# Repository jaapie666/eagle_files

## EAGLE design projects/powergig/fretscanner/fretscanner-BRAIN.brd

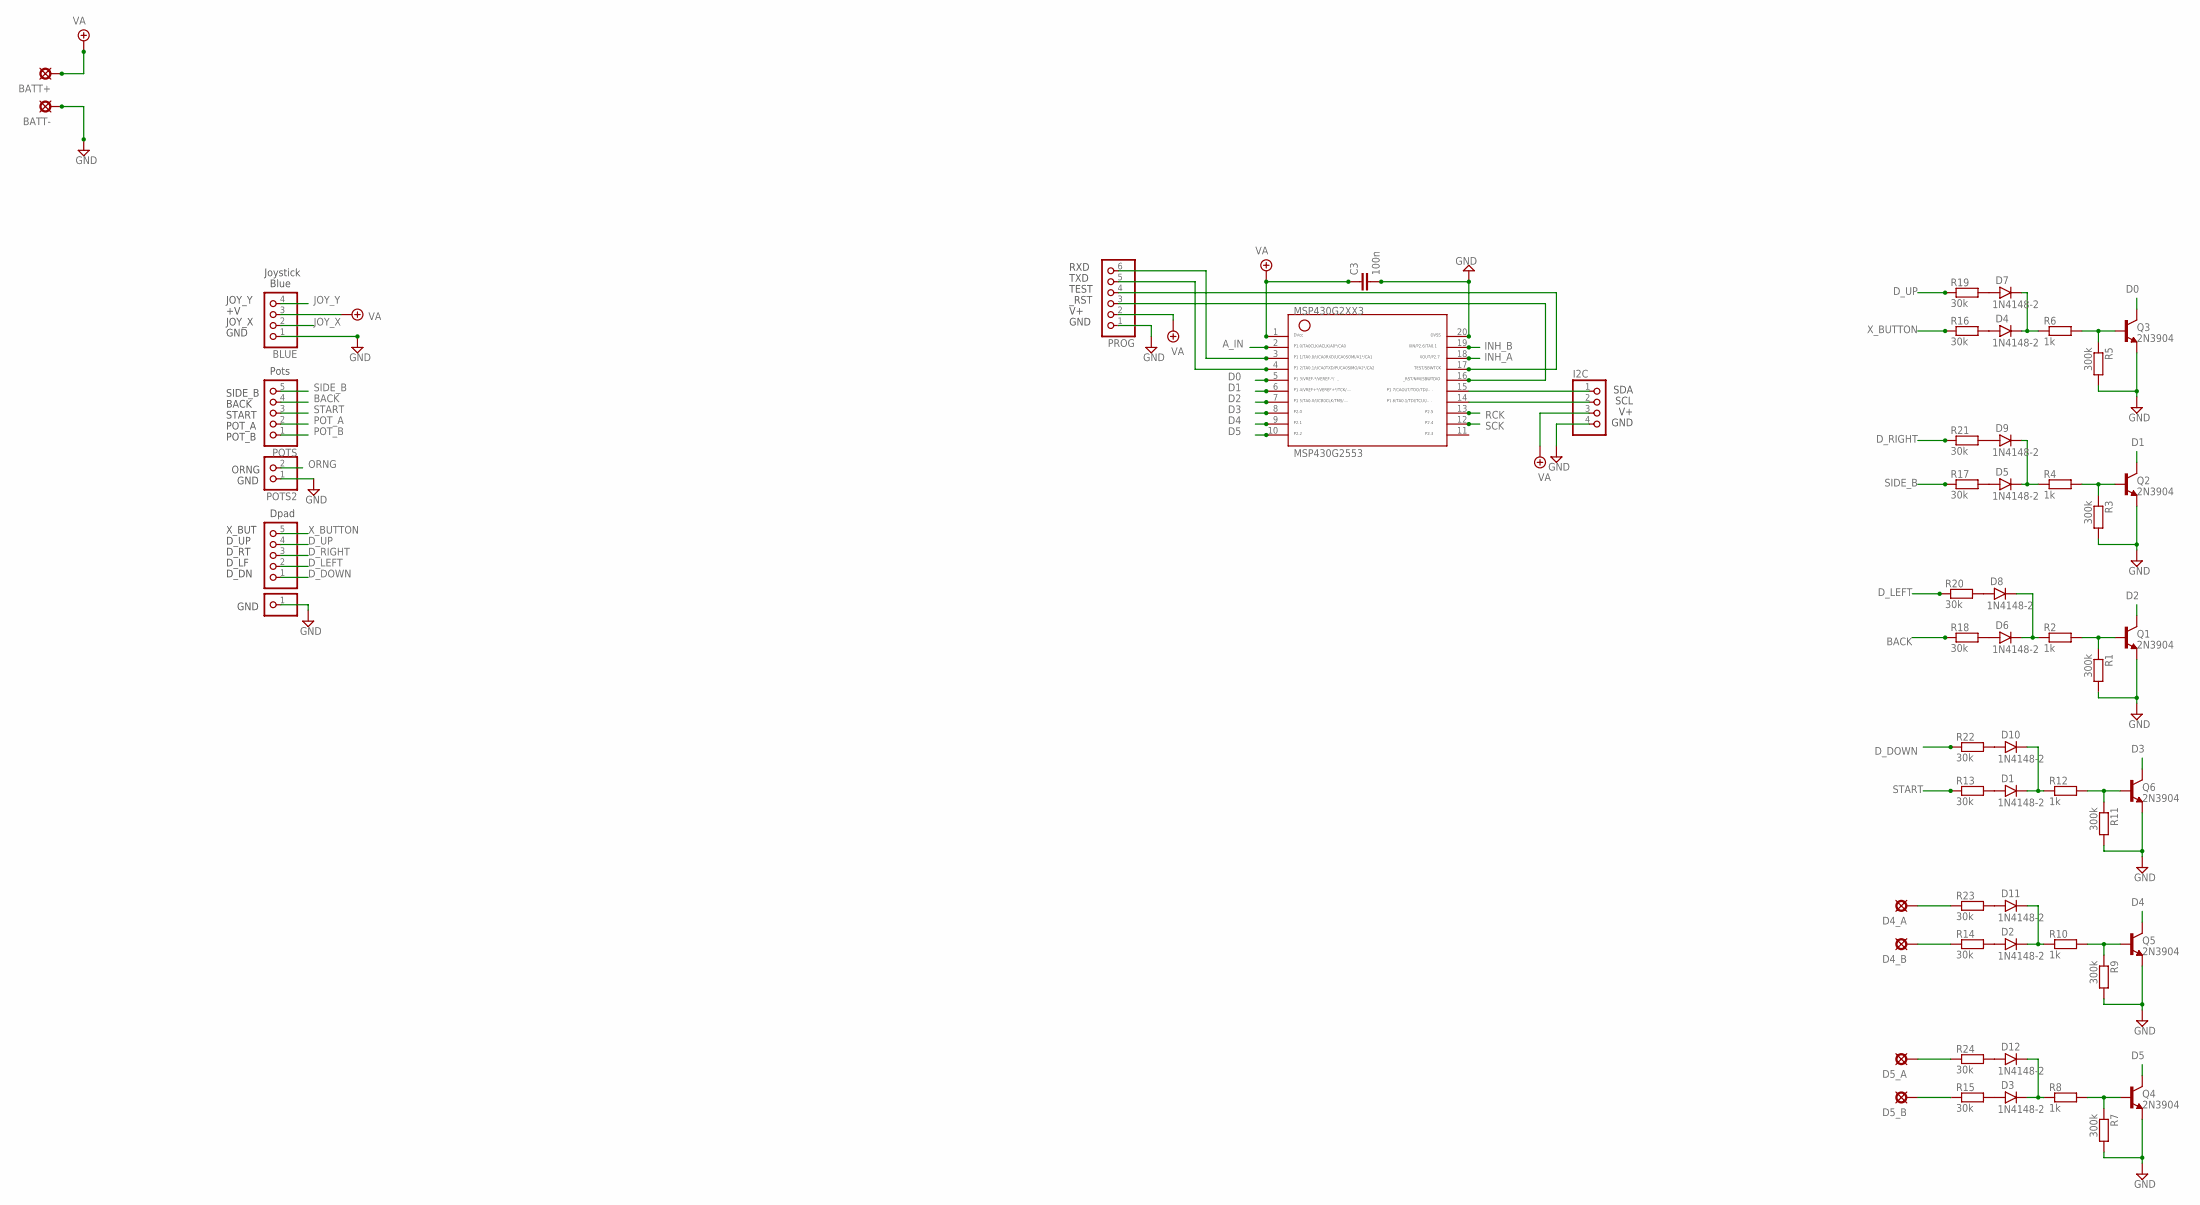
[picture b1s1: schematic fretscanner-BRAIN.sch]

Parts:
BATT+: PADL; LONG
BATT-: PADL; LONG
BLUE: PINHD-1X4; 1X04
C3: 100n; 050X030_050_3
D1, D2, D3, D4, D5, D6, D7, D8, D9, D10, D11, D12: 1N4148-2; DO35-2
D4_A, D4_B, D5_A, D5_B: PAD; SQUARE
DPAD: PINHD-1X5; 1X05
DPAD2: PINHD-1X1; 1X01
I2C: PINHD-1X4; 1X04
MSP430G2553: G2XX3---N20; N20
POTS: PINHD-1X5; 1X05
POTS2: PINHD-1X2; 1X02
PROG: PINHD-1X6; 1X06
Q1, Q2, Q3, Q4, Q5, Q6: 2N3904; TO92-
R1, R3, R5, R7, R9, R11: 300k; R0207/1V
R2, R4, R6, R8, R10, R12: 1k; R0207/3
R13, R14, R15, R16, R17, R18, R19, R20, R21, R22, R23, R24: 30k; R0207/3

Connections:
A_IN: MSP430G2553.2
BACK: POTS.4, R18.1
D0: MSP430G2553.5, Q3.1 (C)
D1: MSP430G2553.6, Q2.1 (C)
D2: MSP430G2553.7, Q1.1 (C)
D3: MSP430G2553.8, Q6.1 (C)
D4: MSP430G2553.9, Q5.1 (C)
D5: MSP430G2553.10, Q4.1 (C)
D_DOWN: DPAD.1, R22.1
D_LEFT: DPAD.2, R20.1
D_RIGHT: DPAD.3, R21.1
D_UP: DPAD.4, R19.1
GND: BATT-.1, BLUE.1, C3.2, DPAD2.1, I2C.4, MSP430G2553.20, POTS2.1, PROG.1, Q1.3 (E), Q2.3 (E), Q3.3 (E), Q4.3 (E), Q5.3 (E), Q6.3 (E), R1.2, R3.2, R5.2, R7.2, R9.2, R11.2
INH_A: MSP430G2553.18
INH_B: MSP430G2553.19
JOY_X: BLUE.2
JOY_Y: BLUE.4
unnamed: I2C.1, MSP430G2553.15
unnamed: Q2.2 (B), R3.1, R4.2
unnamed: D3.A, R15.2
unnamed: D5.C, D9.C, R4.1
unnamed: Q3.2 (B), R5.1, R6.2
unnamed: Q1.2 (B), R1.1, R2.2
unnamed: D6.C, D8.C, R2.1
unnamed: D4.A, R16.2
unnamed: D5.A, R17.2
unnamed: D4.C, D7.C, R6.1
unnamed: Q4.2 (B), R7.1, R8.2
unnamed: D6.A, R18.2
unnamed: D3.C, D12.C, R8.1
unnamed: Q5.2 (B), R9.1, R10.2
unnamed: D1.A, R13.2
unnamed: I2C.2, MSP430G2553.14
unnamed: D2.C, D11.C, R10.1
unnamed: Q6.2 (B), R11.1, R12.2
unnamed: D2.A, R14.2
unnamed: D1.C, D10.C, R12.1
unnamed: D7.A, R19.2
unnamed: D8.A, R20.2
unnamed: D9.A, R21.2
unnamed: D10.A, R22.2
unnamed: D4_B.1, R14.1
unnamed: D5_B.1, R15.1
unnamed: D11.A, R23.2
unnamed: D12.A, R24.2
unnamed: D4_A.1, R23.1
unnamed: D5_A.1, R24.1
ORNG: POTS2.2
POT_A: POTS.2
POT_B: POTS.1
RCK: MSP430G2553.13
RXD: MSP430G2553.3, PROG.6
SCK: MSP430G2553.12
SIDE_B: POTS.5, R17.1
START: POTS.3, R13.1
TEST: MSP430G2553.17, PROG.4
TXD: MSP430G2553.4, PROG.5
VA: BATT+.1, BLUE.3, C3.1, I2C.3, MSP430G2553.1, PROG.2
X_BUTTON: DPAD.5, R16.1
_RST: MSP430G2553.16, PROG.3

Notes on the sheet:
Joystick
Pots
Dpad
Blue
X_BUT
D_UP
D_RT
D_LF
D_DN
GND
SIDE_B
BACK
START
POT_A
POT_B
ORNG
JOY_X
JOY_Y
RXD
TXD
TEST
_RST
SDA
SCL

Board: 2 copper layers, 57 parts (0 on the bottom side), 50 nets, no tracks yet.

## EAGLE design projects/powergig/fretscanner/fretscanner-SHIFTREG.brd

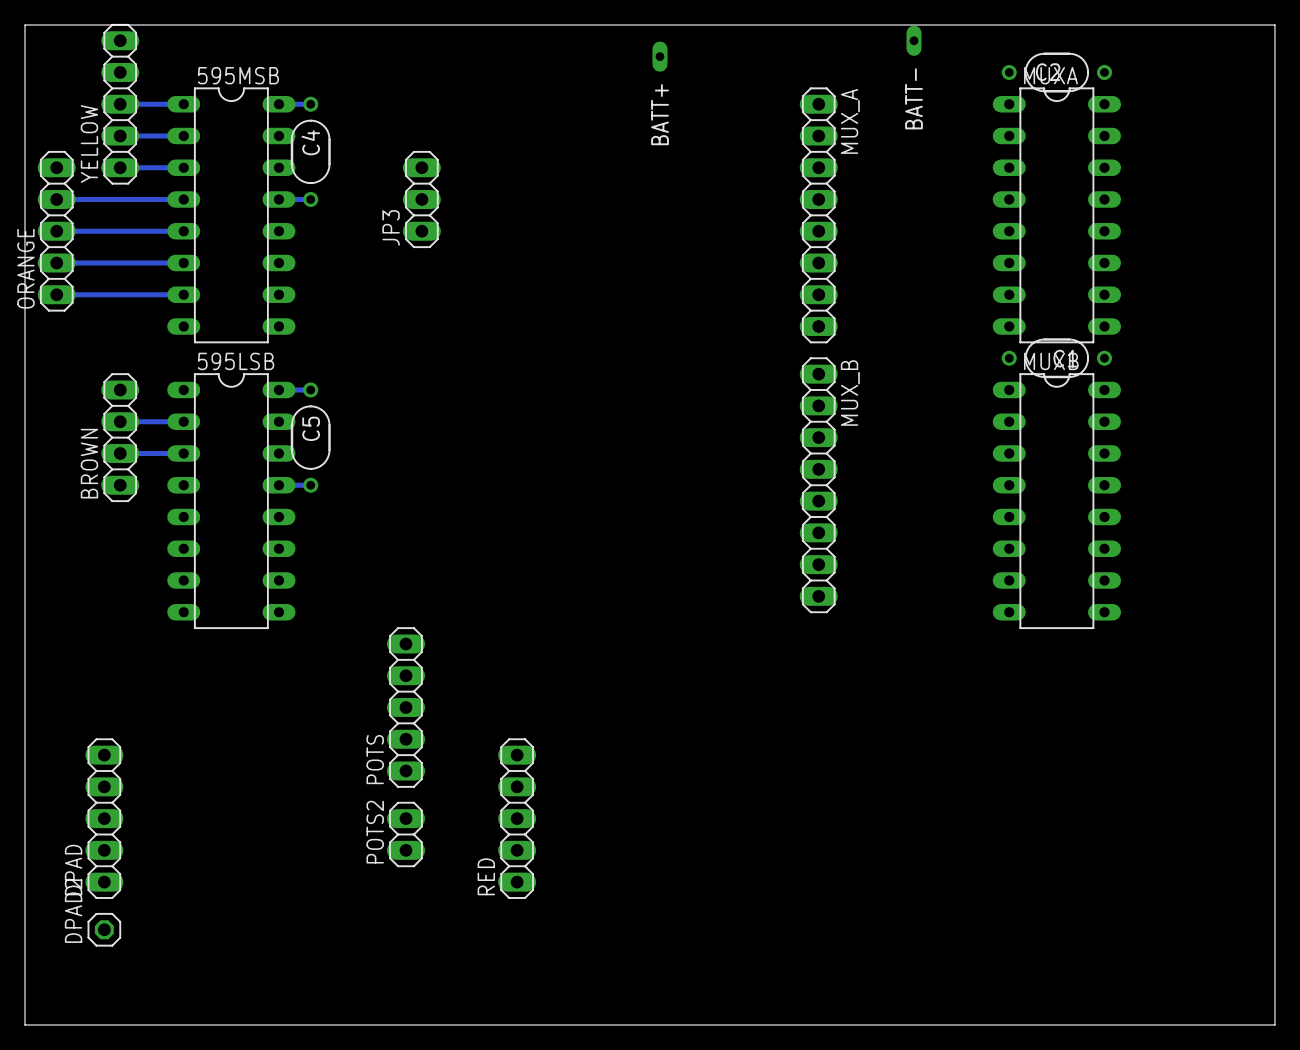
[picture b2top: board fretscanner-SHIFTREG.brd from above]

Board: 2 copper layers, 100.0 x 80.0 mm, 21 parts (0 on the bottom side), 38 nets.

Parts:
595LSB, 595MSB: 74LS595N; DIL16
BATT+: LONG
BATT-: LONG
BROWN: 1X04
C1, C2, C4, C5: 100n; 050X030_050_3
DPAD: 1X05
DPAD2: 1X01
JP3: 1X03
MUXA: 4051N; DIL16
MUXB: 4051N; DIL16
MUX_A: 1X08
MUX_B: 1X08
ORANGE: 1X05
POTS: 1X05
POTS2: 1X02
RED: 1X05
YELLOW: 1X05

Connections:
A_IN: MUXA.3, MUXB.3
GND: 595LSB.8, 595LSB.13, 595MSB.8, 595MSB.13, BATT-.1, BROWN.1, C1.2, C2.2, C4.2, C5.2, DPAD2.1, MUXA.7, MUXA.8, MUXB.7, MUXB.8, POTS2.1
JOY_X: MUXA.4, MUX_A.1
JOY_Y: MUXA.2, MUX_A.2
MUX09: MUXA.13, MUX_A.8
unnamed: 595LSB.14, 595MSB.9
unnamed: MUXA.12, MUX_A.5
unnamed: MUXA.15, MUX_A.6
unnamed: MUXA.14, MUX_A.7
unnamed: MUXB.4, MUX_B.1
unnamed: MUXB.2, MUX_B.2
unnamed: MUXB.5, MUX_B.3
unnamed: MUXB.1, MUX_B.4
unnamed: MUXB.12, MUX_B.5
unnamed: MUXB.15, MUX_B.6
unnamed: MUXB.14, MUX_B.7
unnamed: MUXB.13, MUX_B.8
POT_A: MUXA.5, MUX_A.3, POTS.2
POT_B: MUXA.1, MUX_A.4, POTS.1
RCK: 595LSB.12, 595MSB.12, JP3.2
SCK: 595LSB.11, 595MSB.11, JP3.1
SER: 595MSB.14, JP3.3
SR0: 595LSB.7, MUXA.11, MUXB.11
SR1: 595LSB.6, MUXA.10, MUXB.10
SR2: 595LSB.5, MUXA.9, MUXB.9
SR4: 595LSB.3, BROWN.2
SR5: 595LSB.2, BROWN.3
SR6: 595LSB.1, YELLOW.5
SR7: 595LSB.15, BROWN.4
SR8: 595MSB.7, ORANGE.1
SR9: 595MSB.6, ORANGE.2
SR10: 595MSB.5, ORANGE.3
SR11: 595MSB.4, ORANGE.4
SR12: 595MSB.3, YELLOW.1
SR13: 595MSB.2, YELLOW.2
SR14: 595MSB.1, YELLOW.3
SR15: 595MSB.15, YELLOW.4
VA: 595LSB.10, 595LSB.16, 595MSB.10, 595MSB.16, BATT+.1, C1.1, C2.1, C4.1, C5.1, MUXA.16, MUXB.16

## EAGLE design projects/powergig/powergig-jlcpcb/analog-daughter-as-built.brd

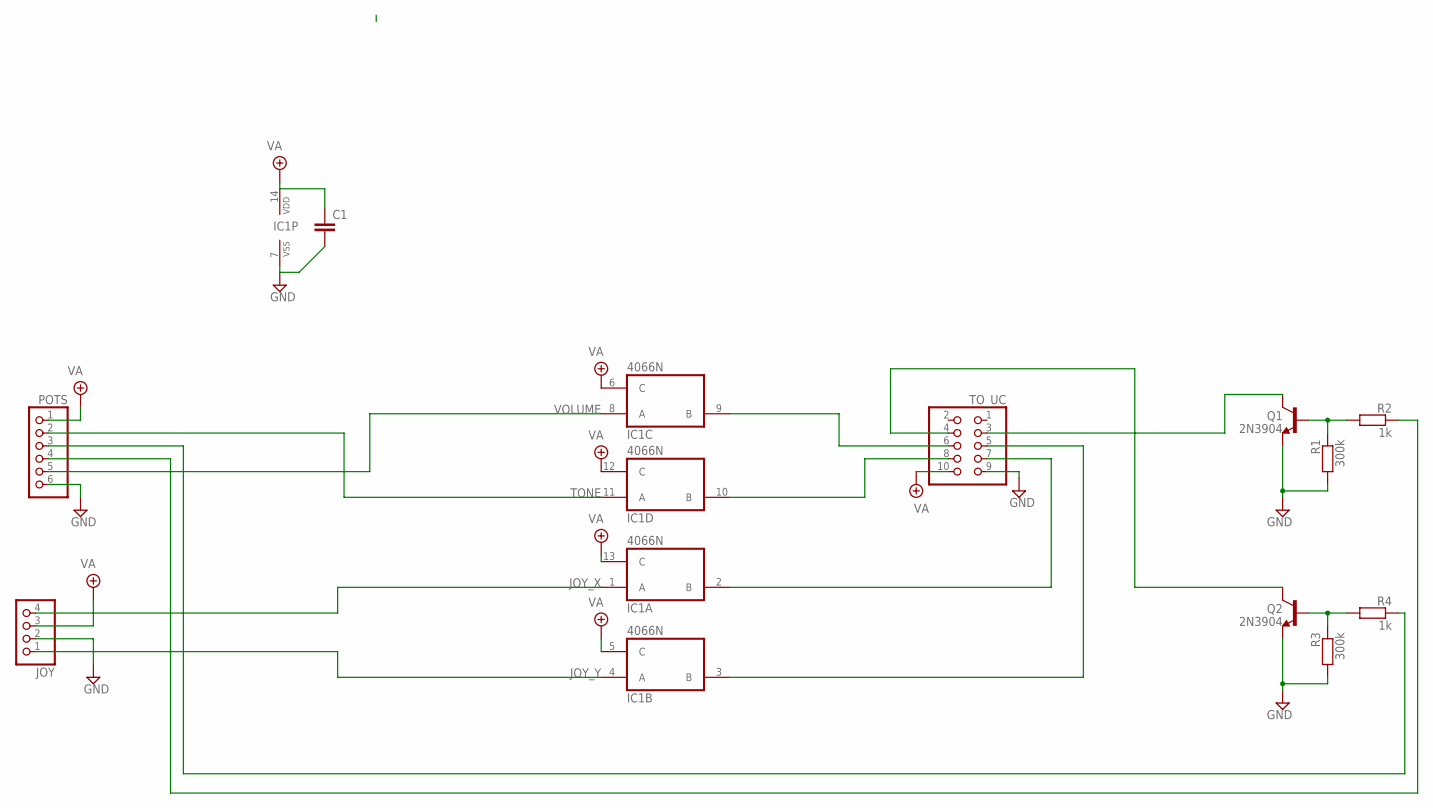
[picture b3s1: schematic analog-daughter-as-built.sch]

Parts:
C1: 050X030_0251; 050X030_025
IC1: 4066N; DIL14
JOY: PINHD-1X4; 1X04
POTS: PINHD-1X6; 1X06
Q1, Q2: 2N3904; TO92-
R1, R3: 300k; R0207/3
R2, R4: 1k; R0207/3
TO_UC: PINHD-2X5IDC; 10PIN_IDC

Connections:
GND: C1.2, IC1.7 (VSS), JOY.2, POTS.6, Q1.3 (E), Q2.3 (E), R1.2, R3.2, TO_UC.9
JOY_X: IC1.1 (A), JOY.4
JOY_Y: IC1.4 (A), JOY.1
unnamed: Q1.1 (C), TO_UC.3
unnamed: IC1.9 (B), TO_UC.6
unnamed: IC1.10 (B), TO_UC.8
unnamed: IC1.2 (B), TO_UC.7
unnamed: IC1.3 (B), TO_UC.5
unnamed: Q2.1 (C), TO_UC.4
unnamed: Q1.2 (B), R1.1, R2.2
unnamed: Q2.2 (B), R3.1, R4.2
TONE: IC1.11 (A), POTS.2
TONE_BUTTON: POTS.3, R4.1
VA: C1.1, IC1.5 (C), IC1.6 (C), IC1.12 (C), IC1.13 (C), IC1.14 (VDD), JOY.3, POTS.1, TO_UC.10
VOLUME: IC1.8 (A), POTS.5
VOL_BUTTON: POTS.4, R2.1

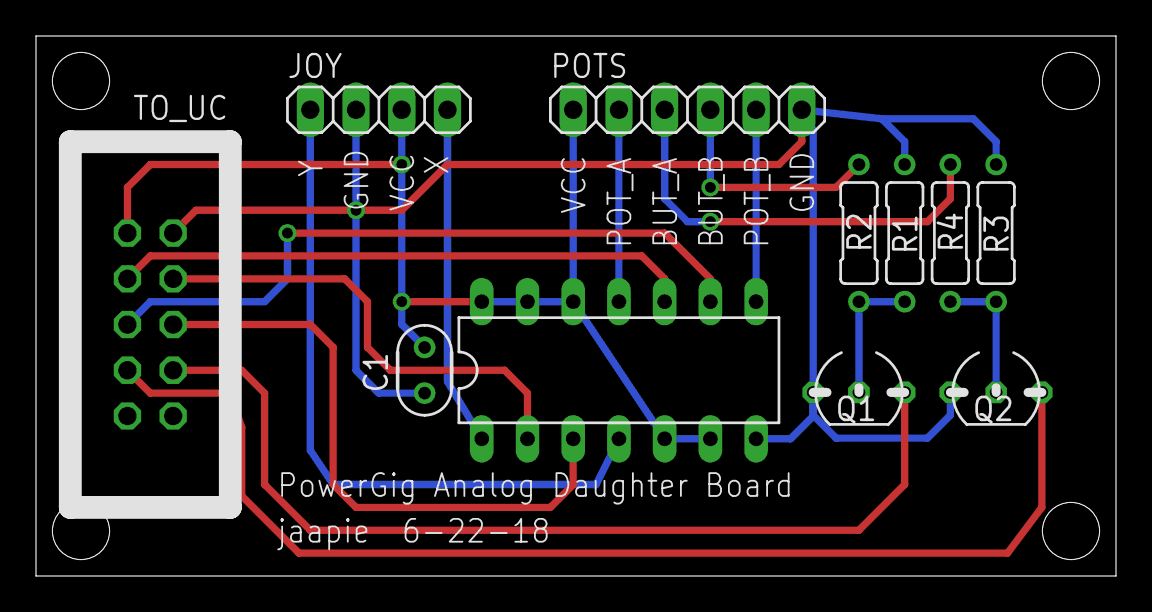
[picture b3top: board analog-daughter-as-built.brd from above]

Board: 2 copper layers, 60.0 x 30.0 mm, 11 parts (0 on the bottom side), 16 nets.

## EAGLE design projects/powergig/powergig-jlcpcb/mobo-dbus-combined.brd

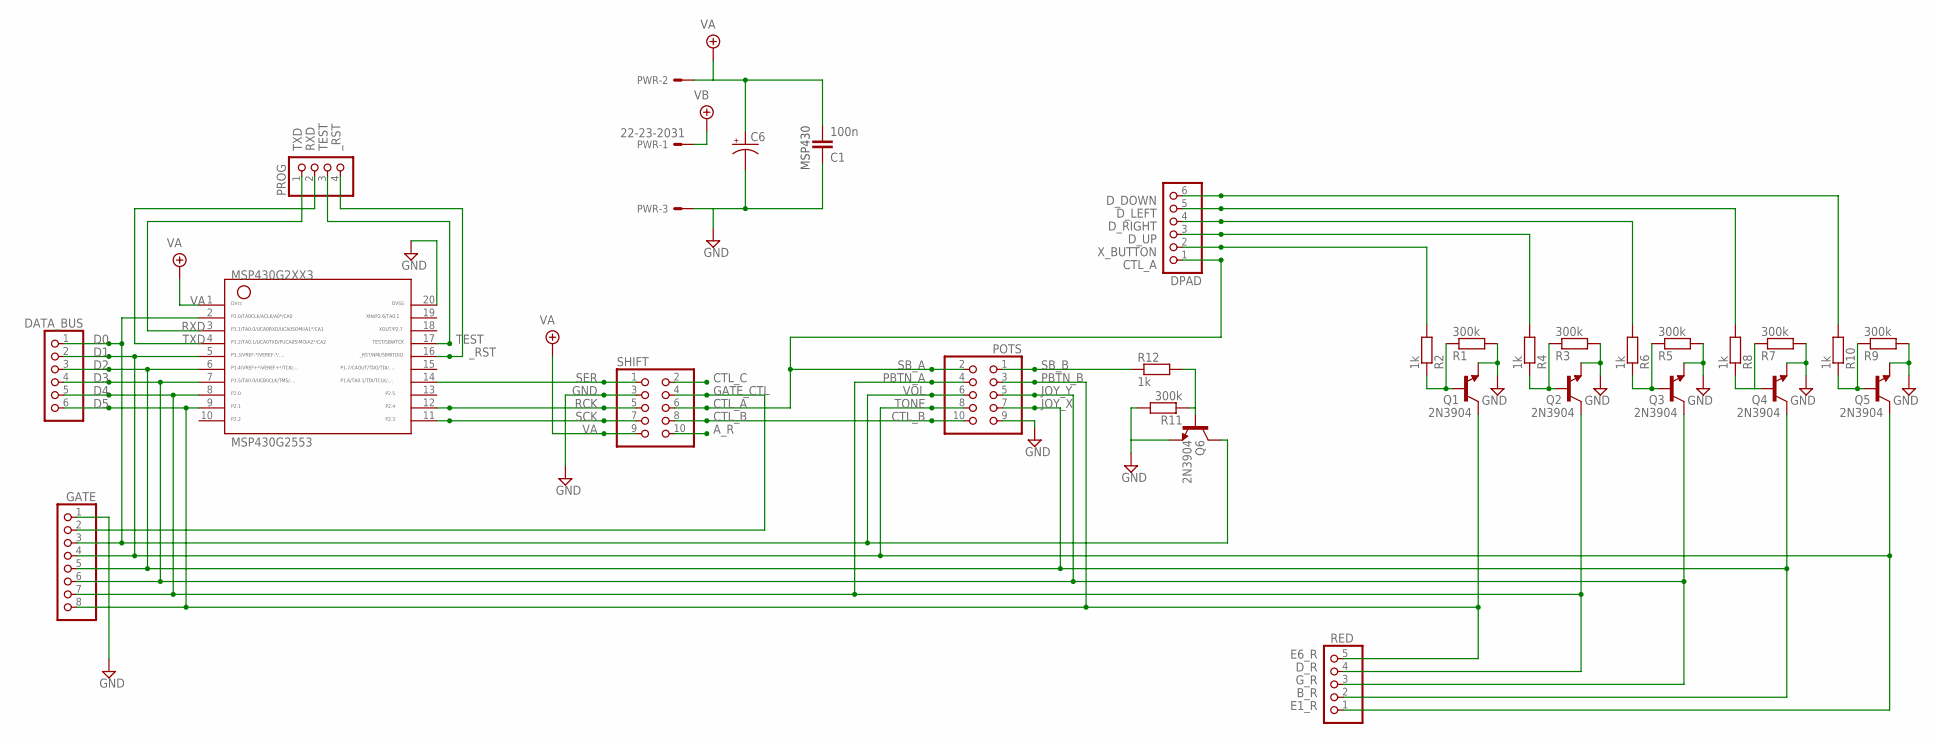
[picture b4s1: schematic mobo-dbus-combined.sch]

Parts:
C1: 100n; 050X030_050_3
C6: 0501; 050_020_1
DATA_BUS: PINHD-1X6; 1X06
DPAD: PINHD-1X6; 1X06
GATE: PINHD-1X8; 1X08
MSP430G2553: G2XX3---N20; N20
POTS: PINHD-2X5; 2X05
PROG: PINHD-1X4; 1X04
PWR: 22-23-2031
Q1, Q2, Q3, Q4, Q5, Q6: 2N3904; TO92-
R1, R3, R5, R7, R9, R11: 300k; R0207/1V
R2, R4, R6, R8, R10, R12: 1k; R0207/1V
RED: PINHD-1X5; 1X05
SHIFT: PINHD-2X5; 2X05

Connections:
CTL_A: DPAD.1, POTS.2, SHIFT.6
CTL_B: POTS.10, SHIFT.8
CTL_C: SHIFT.2
D0: DATA_BUS.1, GATE.3, MSP430G2553.2, POTS.6, Q6.1 (C), SHIFT.10
D1: DATA_BUS.2, GATE.4, MSP430G2553.5, POTS.8, Q5.1 (C), RED.1
D2: DATA_BUS.3, GATE.5, MSP430G2553.6, POTS.7, Q4.1 (C), RED.2
D3: DATA_BUS.4, GATE.6, MSP430G2553.7, POTS.5, Q3.1 (C), RED.3
D4: DATA_BUS.5, GATE.7, MSP430G2553.8, POTS.4, Q2.1 (C), RED.4
D5: DATA_BUS.6, GATE.8, MSP430G2553.9, POTS.3, Q1.1 (C), RED.5
D_DOWN: DPAD.6, R10.2
D_LEFT: DPAD.5, R8.2
D_RIGHT: DPAD.4, R6.2
D_UP: DPAD.3, R4.2
GATE_CTL: GATE.2, SHIFT.4
GND: C1.1, C6.-, GATE.1, MSP430G2553.20, POTS.9, PWR.3, Q1.3 (E), Q2.3 (E), Q3.3 (E), Q4.3 (E), Q5.3 (E), Q6.3 (E), R1.2, R3.2, R5.2, R7.2, R9.2, R11.2, SHIFT.3
unnamed: Q6.2 (B), R11.1, R12.2
unnamed: Q1.2 (B), R1.1, R2.1
unnamed: Q2.2 (B), R3.1, R4.1
unnamed: Q3.2 (B), R5.1, R6.1
unnamed: Q4.2 (B), R7.1, R8.1
unnamed: Q5.2 (B), R9.1, R10.1
unnamed: POTS.1, R12.1
RCK: MSP430G2553.12, SHIFT.5
RXD: MSP430G2553.3, PROG.1
SCK: MSP430G2553.11, SHIFT.7
SER: MSP430G2553.14, SHIFT.1
TEST: MSP430G2553.17, PROG.3
TXD: MSP430G2553.4, PROG.2
VA: C1.2, C6.+, MSP430G2553.1, PWR.2, SHIFT.9
VB: PWR.1
X_BUTTON: DPAD.2, R2.2
_RST: MSP430G2553.16, PROG.4

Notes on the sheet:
MSP430
A_R
E6_R
D_R
G_R
B_R
E1_R
TONE
VOL
PBTN_A
PBTN_B
JOY_X
JOY_Y
SB_A
CTL_B
SB_B
CTL_A

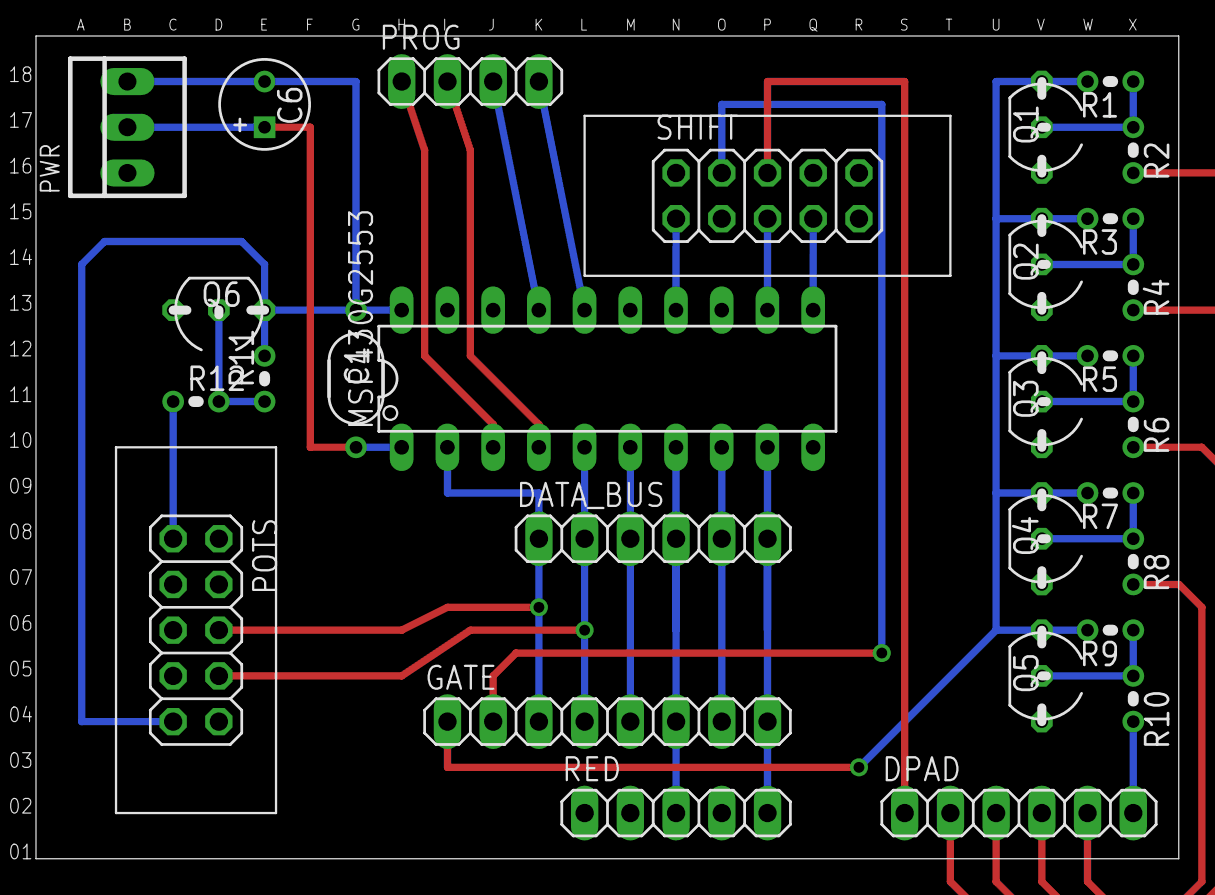
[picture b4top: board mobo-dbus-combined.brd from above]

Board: 2 copper layers, 63.5 x 45.7 mm, 29 parts (0 on the bottom side), 30 nets.

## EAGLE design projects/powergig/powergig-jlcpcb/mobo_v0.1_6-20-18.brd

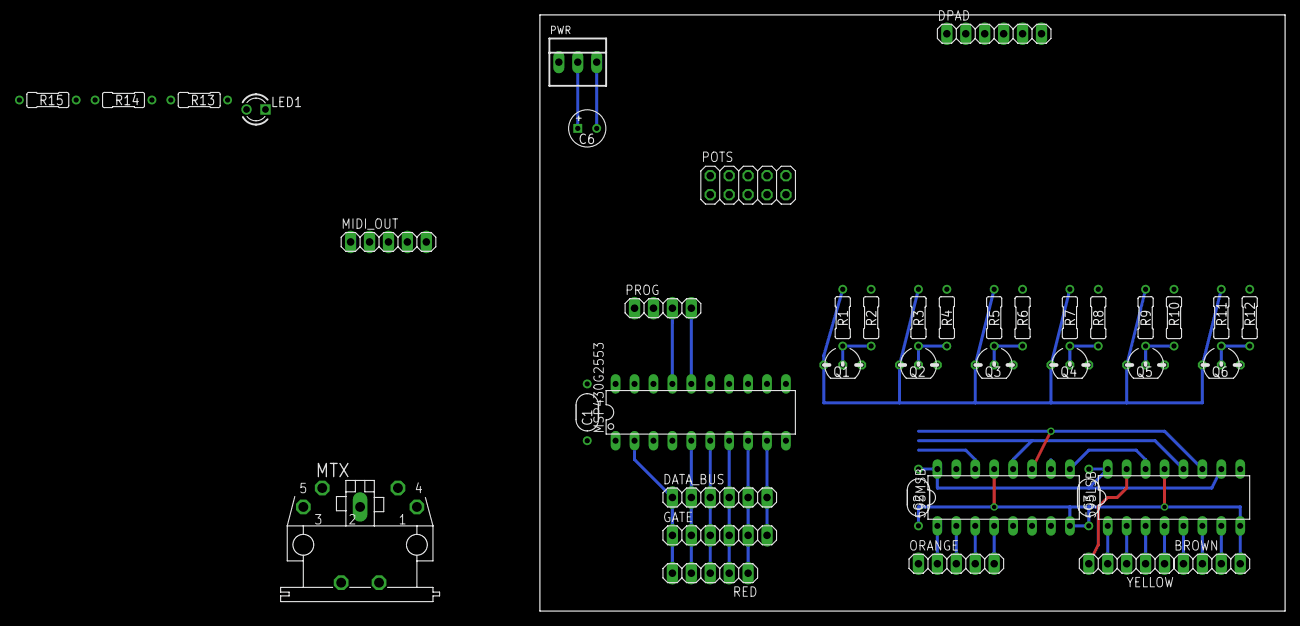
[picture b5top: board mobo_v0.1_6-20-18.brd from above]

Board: 2 copper layers, 100.0 x 80.0 mm, 41 parts (0 on the bottom side), 46 nets.

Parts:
595LSB, 595MSB: 74LS595N; DIL16
BROWN: 1X04
C1, C2, C3: 100n; 050X030_050_3
C6: 050_020_1
DATA_BUS: 1X06
DPAD: 1X06
GATE: 1X06
LED1: LED3MM
MIDI_OUT: 1X05
MSP430G2553: G2XX3---N20; N20
MTX: MAB5SH
ORANGE: 1X05
POTS: 2X05
PROG: 1X04
PWR: 22-23-2031
Q1, Q2, Q3, Q4, Q5, Q6: 2N3904; TO92-
R1, R3, R5, R7, R9, R11: 300k; R0207/3
R2, R4, R6, R8, R10, R12: 1k; R0207/3
R13, R14: 47R; R0207/3
R15: 120R; R0207/3
RED: 1X05
YELLOW: 1X05

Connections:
ANALOG_CTL: 595MSB.7, POTS.10
BUTTON_CTL: 595MSB.6, DPAD.1, POTS.2
D0: DATA_BUS.1, GATE.1, MSP430G2553.2, POTS.6, Q6.1, RED.5
D1: DATA_BUS.2, GATE.2, MSP430G2553.5, POTS.8, Q5.1, RED.4
D2: DATA_BUS.3, GATE.3, MSP430G2553.6, POTS.7, Q4.1, RED.3
D3: DATA_BUS.4, GATE.4, MSP430G2553.7, POTS.5, Q3.1, RED.2
D4: DATA_BUS.5, GATE.5, MSP430G2553.8, POTS.4, Q2.1, RED.1
D5: DATA_BUS.6, GATE.6, MSP430G2553.9, ORANGE.1, POTS.3, Q1.1
D_DOWN: DPAD.6, R10.2
D_LEFT: DPAD.5, R8.2
D_RIGHT: DPAD.4, R6.2
D_UP: DPAD.3, R4.2
GND: 595LSB.8, 595LSB.13, 595MSB.8, 595MSB.13, BROWN.4, C1.1, C2.1, C3.1, C6.-, MIDI_OUT.2, MSP430G2553.20, MTX.2, POTS.9, PWR.3, Q1.3, Q2.3, Q3.3, Q4.3, Q5.3, Q6.3, R1.2, R3.2, R5.2, R7.2, R9.2, R11.2
MIDI_OUT+: MIDI_OUT.4, MTX.4, R13.1
MIDI_OUT-: MIDI_OUT.5, MTX.5, R14.1
M_F1: 595LSB.1, YELLOW.4
M_F2: 595LSB.2, YELLOW.3
M_F3: 595LSB.3, YELLOW.2
M_F4: 595LSB.4, YELLOW.1
M_F5: 595MSB.4, ORANGE.5
M_F6: 595MSB.3, ORANGE.4
M_F7: 595MSB.2, ORANGE.3
M_F8: 595MSB.1, ORANGE.2
M_F9: 595LSB.7, BROWN.3
M_F10: 595LSB.15, YELLOW.5
M_F11: 595LSB.6, BROWN.2
M_F12: 595LSB.5, BROWN.1
unnamed: Q6.2, R11.1, R12.1
unnamed: 595LSB.14, 595MSB.9
unnamed: LED1.A, R15.1
unnamed: Q1.2, R1.1, R2.1
unnamed: Q2.2, R3.1, R4.1
unnamed: Q3.2, R5.1, R6.1
unnamed: Q4.2, R7.1, R8.1
unnamed: Q5.2, R9.1, R10.1
PE: MTX.PE, MTX.PE@
RCK: 595LSB.12, 595MSB.12, MSP430G2553.12
RXD: MSP430G2553.3, PROG.2
SB_2: POTS.1, R12.2
SCK: 595LSB.11, 595MSB.11, MSP430G2553.11
SER: 595MSB.14, MSP430G2553.13
TEST: MSP430G2553.17, PROG.3
TXD: LED1.K, MSP430G2553.4, PROG.1, R14.2
VA: 595LSB.10, 595LSB.16, 595MSB.10, 595MSB.16, C1.2, C2.2, C3.2, C6.+, MSP430G2553.1, PWR.2, R13.2, R15.2
X_BUTTON: DPAD.2, R2.2
_RST: MSP430G2553.16, PROG.4
